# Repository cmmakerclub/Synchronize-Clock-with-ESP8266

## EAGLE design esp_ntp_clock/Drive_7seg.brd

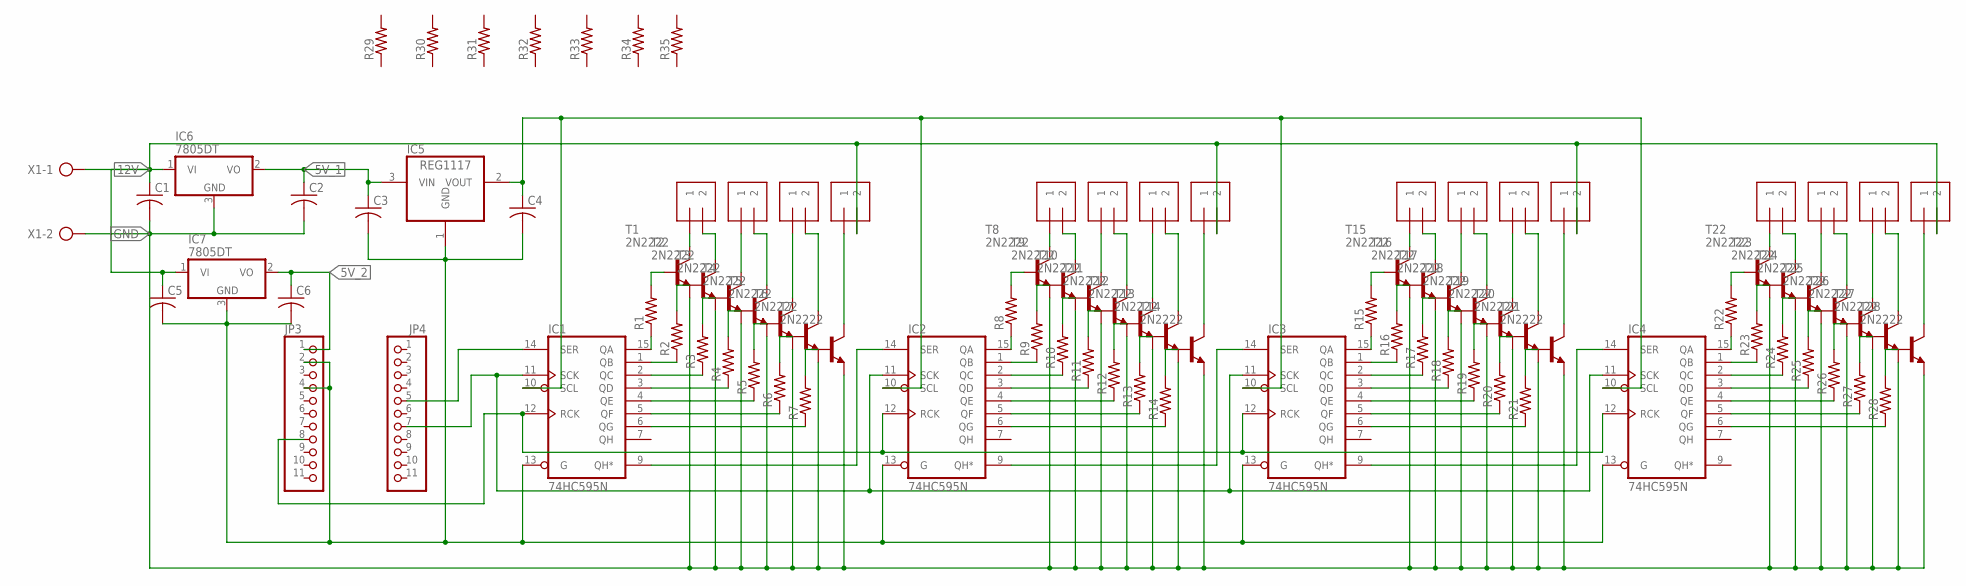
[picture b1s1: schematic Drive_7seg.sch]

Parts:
C1, C2, C3, C4, C5, C6: C-USC0805K; C0805K
IC1, IC2, IC3, IC4: 74HC595N; DIL16
IC5: REG1117; SOT223
IC6, IC7: 7805DT; TO252
J1, J2, J3, J4, J5, J6, J7, J8, J9, J10, J11, J12, J13, J14, J15, J16: 1X2-3.5MM
JP3, JP4: PINHD-1X11; 1X11
R1, R2, R3, R4, R5, R6, R7, R8, R9, R10, R11, R12, R13, R14, R15, R16, R17, R18, R19, R20, R21, R22, R23, R24, R25, R26, R27, R28, R29, R30, R31, R32, R33, R34, R35: R-US_0204/7; 0204/7
T1, T2, T3, T4, T5, T6, T7, T8, T9, T10, T11, T12, T13, T14, T15, T16, T17, T18, T19, T20, T21, T22, T23, T24, T25, T26, T27, T28: 2N2222; TO92-EBC-OVAL
X1: AK300/2

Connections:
5V_1: C2.1, C3.1, IC5.3 (VIN), IC6.2 (VO)
5V_2: C6.1, IC7.2 (VO), JP3.1
12V: C1.1, C5.1, IC6.1 (VI), IC7.1 (VI), J4.2, J8.2, J12.2, J16.2, X1.1
GND: C1.2, C2.2, C3.2, C4.2, C5.2, C6.2, IC1.8 (GND), IC1.13 (G), IC2.8 (GND), IC2.13 (G), IC3.8 (GND), IC3.13 (G), IC4.8 (GND), IC4.13 (G), IC5.1 (GND), IC6.3 (GND), IC7.3 (GND), JP3.2, JP3.4, T1.E, T2.E, T3.E, T4.E, T5.E, T6.E, T7.E, T8.E, T9.E, T10.E, T11.E, T12.E, T13.E, T14.E, T15.E, T16.E, T17.E, T18.E, T19.E, T20.E, T21.E, T22.E, T23.E, T24.E, T25.E, T26.E, T27.E, T28.E, X1.2
unnamed: R1.2, T1.B
unnamed: R2.2, T2.B
unnamed: R3.2, T3.B
unnamed: R4.2, T4.B
unnamed: R5.2, T5.B
unnamed: R6.2, T6.B
unnamed: R7.2, T7.B
unnamed: IC1.15 (QA), R1.1
unnamed: IC1.1 (QB), R2.1
unnamed: IC1.2 (QC), R3.1
unnamed: IC1.3 (QD), R4.1
unnamed: IC1.4 (QE), R5.1
unnamed: IC1.5 (QF), R6.1
unnamed: IC1.6 (QG), R7.1
unnamed: IC1.9 (QH*), IC2.14 (SER)
unnamed: IC2.9 (QH*), IC3.14 (SER)
unnamed: IC3.9 (QH*), IC4.14 (SER)
unnamed: IC1.12 (RCK), IC2.12 (RCK), IC3.12 (RCK), IC4.12 (RCK), JP3.8
unnamed: IC1.11 (SCK), IC2.11 (SCK), IC3.11 (SCK), IC4.11 (SCK), JP4.7
unnamed: IC1.14 (SER), JP4.5
unnamed: J1.1, T1.C
unnamed: J1.2, T2.C
unnamed: J2.1, T3.C
unnamed: J2.2, T4.C
unnamed: J3.1, T5.C
unnamed: J3.2, T6.C
unnamed: J4.1, T7.C
unnamed: R9.2, T9.B
unnamed: R10.2, T10.B
unnamed: R8.2, T8.B
unnamed: R11.2, T11.B
unnamed: R12.2, T12.B
unnamed: R13.2, T13.B
unnamed: R14.2, T14.B
unnamed: IC2.15 (QA), R8.1
unnamed: IC2.1 (QB), R9.1
unnamed: IC2.2 (QC), R10.1
unnamed: IC2.3 (QD), R11.1
unnamed: IC2.4 (QE), R12.1
unnamed: IC2.5 (QF), R13.1
unnamed: IC2.6 (QG), R14.1
unnamed: J5.1, T8.C
unnamed: J5.2, T9.C
unnamed: J6.1, T10.C
unnamed: J6.2, T11.C
unnamed: J7.1, T12.C
unnamed: J7.2, T13.C
unnamed: J8.1, T14.C
unnamed: R16.2, T16.B
unnamed: R17.2, T17.B
unnamed: R15.2, T15.B
unnamed: R18.2, T18.B
unnamed: R19.2, T19.B
unnamed: R20.2, T20.B
unnamed: R21.2, T21.B
unnamed: IC3.15 (QA), R15.1
unnamed: IC3.1 (QB), R16.1
unnamed: IC3.2 (QC), R17.1
unnamed: IC3.3 (QD), R18.1
unnamed: IC3.4 (QE), R19.1
unnamed: IC3.5 (QF), R20.1
unnamed: IC3.6 (QG), R21.1
unnamed: J9.1, T15.C
unnamed: J9.2, T16.C
unnamed: J10.1, T17.C
unnamed: J10.2, T18.C
unnamed: J11.1, T19.C
unnamed: J11.2, T20.C
unnamed: J12.1, T21.C
unnamed: R23.2, T23.B
unnamed: R24.2, T24.B
unnamed: R22.2, T22.B
unnamed: R25.2, T25.B
unnamed: R26.2, T26.B
unnamed: R27.2, T27.B
unnamed: R28.2, T28.B
unnamed: IC4.15 (QA), R22.1
unnamed: IC4.1 (QB), R23.1
unnamed: IC4.2 (QC), R24.1
unnamed: IC4.3 (QD), R25.1
unnamed: IC4.4 (QE), R26.1
unnamed: IC4.5 (QF), R27.1
unnamed: IC4.6 (QG), R28.1
unnamed: J13.1, T22.C
unnamed: J13.2, T23.C
unnamed: J14.1, T24.C
unnamed: J14.2, T25.C
unnamed: J15.1, T26.C
unnamed: J15.2, T27.C
unnamed: J16.1, T28.C
VCC: C4.1, IC1.10 (SCL), IC1.16 (VCC), IC2.10 (SCL), IC2.16 (VCC), IC3.10 (SCL), IC3.16 (VCC), IC4.10 (SCL), IC4.16 (VCC), IC5.2 (VOUT)

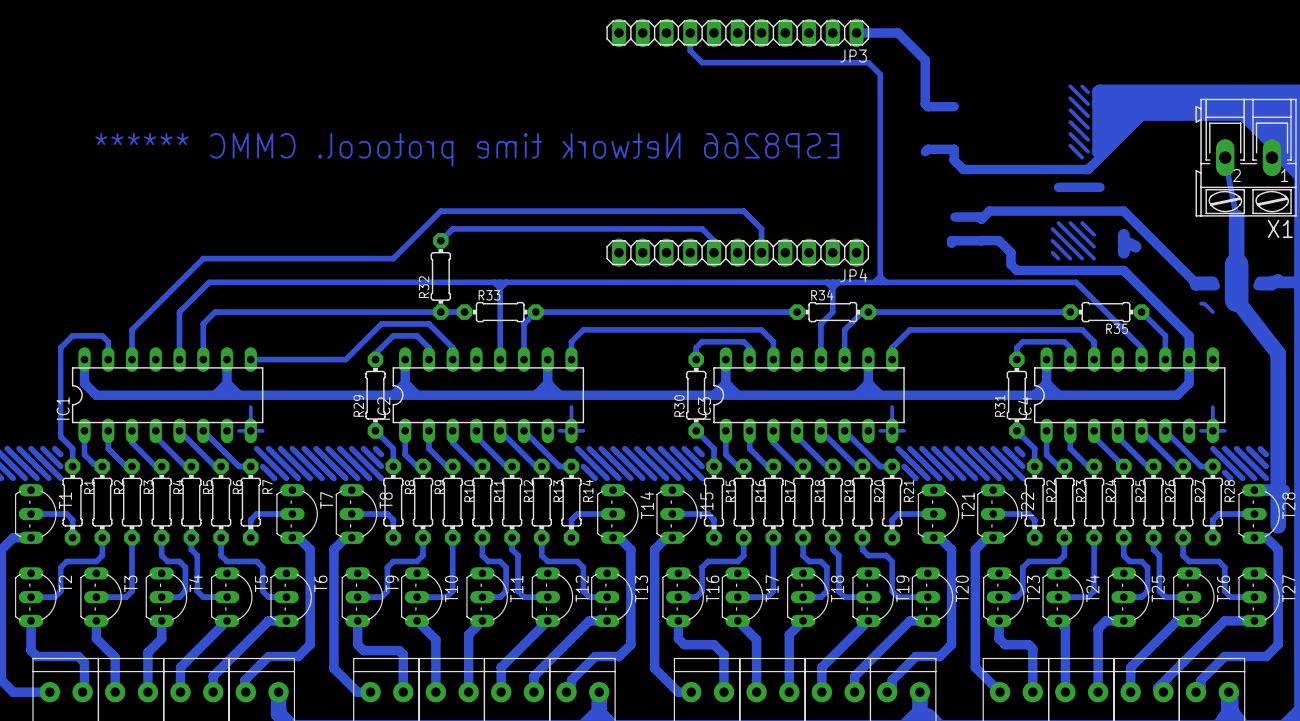
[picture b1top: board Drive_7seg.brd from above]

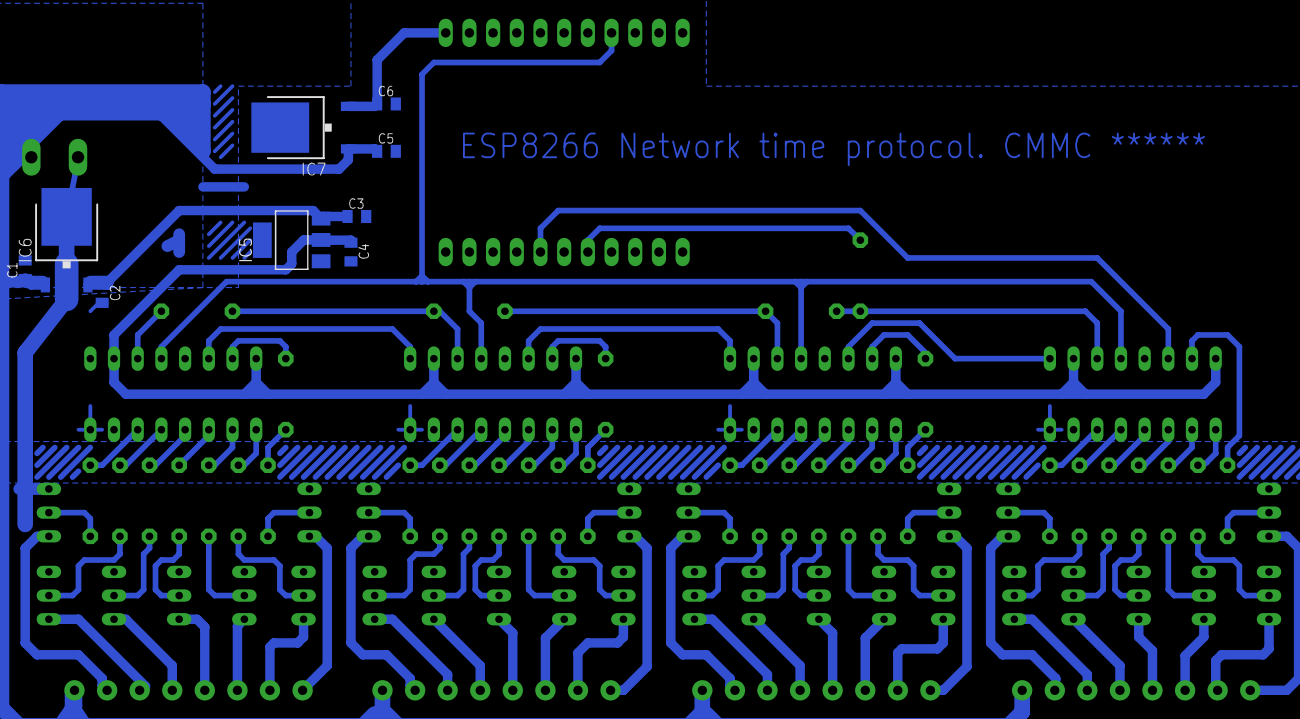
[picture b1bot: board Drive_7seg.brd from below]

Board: 2 copper layers, 95 parts (9 on the bottom side), 95 nets.

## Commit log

2015-08-05 v1 ss update time from internet every 1s
2015-08-09 version 1
2015-08-09 เพิ่มวงจร
2015-08-09 force read & 2hz update rate
2015-08-09 no message
